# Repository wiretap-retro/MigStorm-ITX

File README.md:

# MigStorm-ITX
A 68000 socketed ITX form factor Minimig.

## Info
Tested by Zenon to boot with Pistorm and CaffeineOS, also with a regular M68k CPU. It appears to be fully working, and I've received feedback from at least 10 people that it is working well in their testing. It could use more general trace cleanup/enhancement, but works as-is.

## Mouser Cart
https://www.mouser.com/ProjectManager/ProjectDetail.aspx?AccessID=da74540bb5 \
At the time of making the Mouser cart, all parts were in stock. If parts go out of stock, EOL, have a part number change, or have a minimum order quantity change -- seach for equivalent replacements or they may be able to be sourced from Arrow and Digikey. I recommend using Octopart and other similar sites to search for parts if you can't find something. I caution using sources like Ebay and Aliexpress for key components, especially from China-based sellers with little to no feedback since they'll often sell counterfeit items. Sometimes you get lucky, sometimes you don't. Primary/authorized retailers are highly recommended for component purchases so you do less troubleshooting and can spend more time playing. \
\
As a DIY project, total cost for all parts and a board should come out to just under $150. (plus the cost of a CPU/Pistorm, power supply, and case) \
\
An interactive HTML BOM has been added to the main repository to assist with building.

## Other / Misc. Contributions
jjsaenz1969's 3D printed case for Migstorm: https://www.thingiverse.com/thing:7063501

## Rev History
v0.6 -- Current rev to build. Updated PS/2 Mouse & Keyboard to use redundant clock & data lines due to issues with some keyboards and mice using splitter style pinout. \
v0.5 -- Updated silkscreen for capacitor polarity upon community request. Updated iBOM and BOM. \
v0.4 -- Corrected PS/2 Mouse & Keyboard pwr/gnd pinout. \
v0.3 -- Changed soft-power circuit from 555 timer to a MAX16054, cleaned up a few traces with lots of vias. Still need more cleanup. [depreciated rev, do not build] \
v0.2 -- Initial rev with corrected 68k socket size. [depreciated rev, do not build] \
v0.1 -- Alpha release, incorrect 68k footprint width. [depreciated, removed]

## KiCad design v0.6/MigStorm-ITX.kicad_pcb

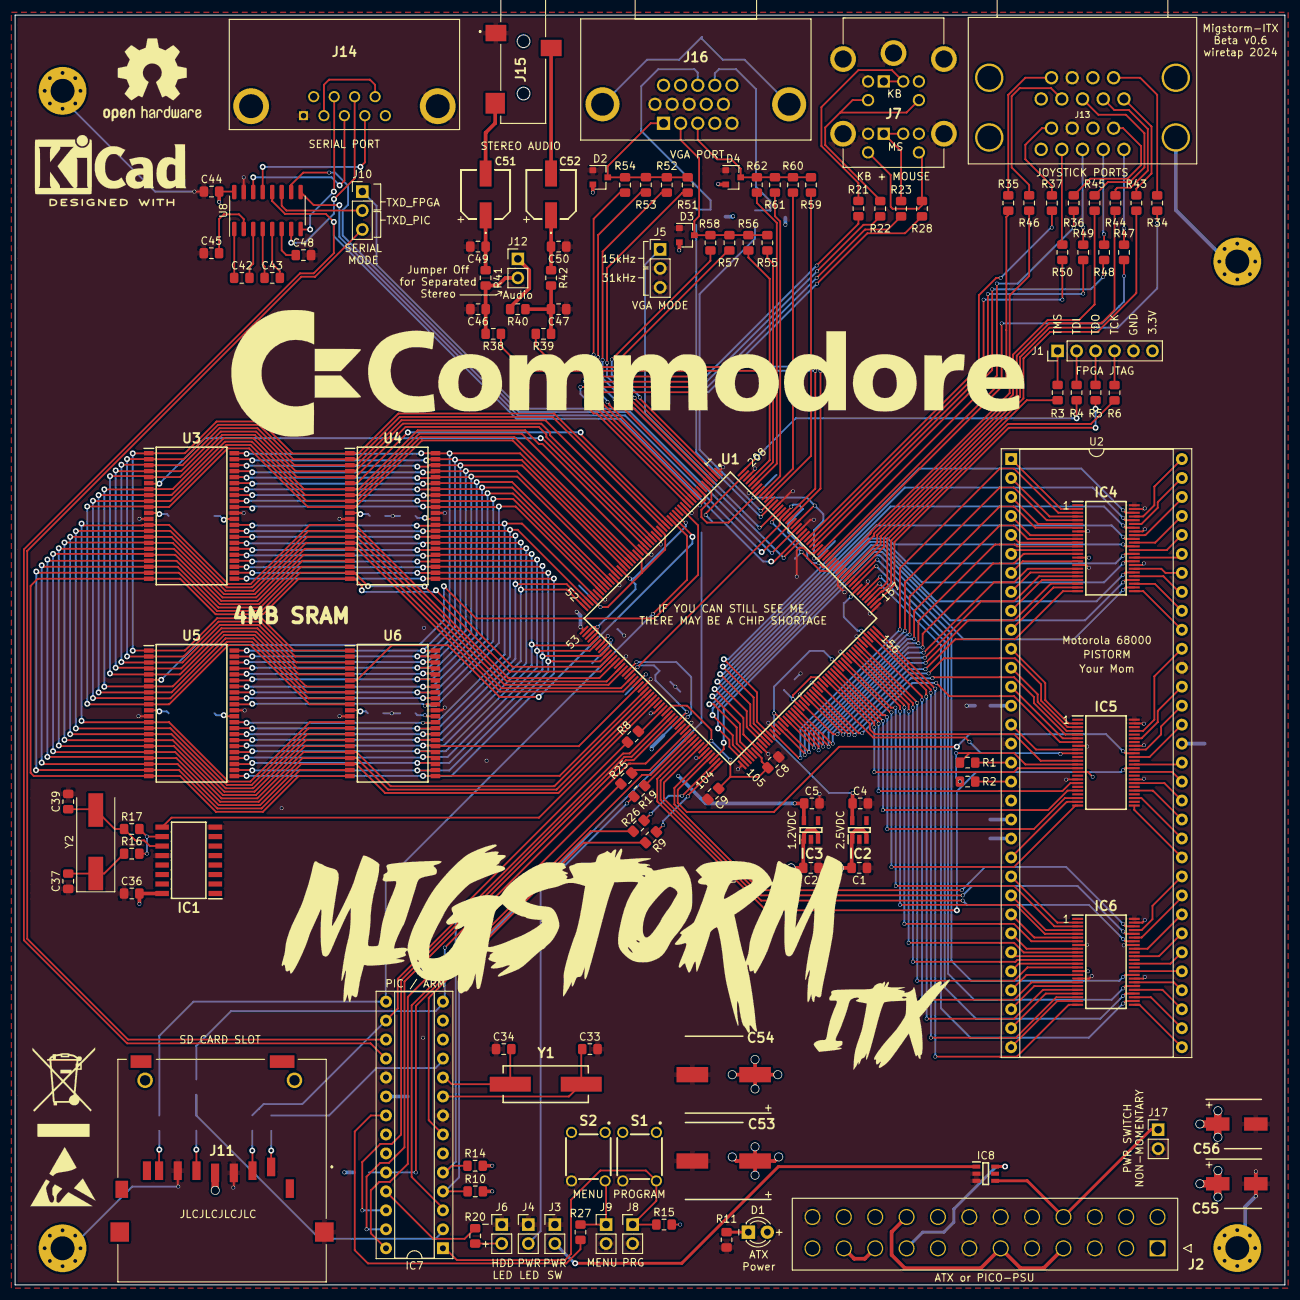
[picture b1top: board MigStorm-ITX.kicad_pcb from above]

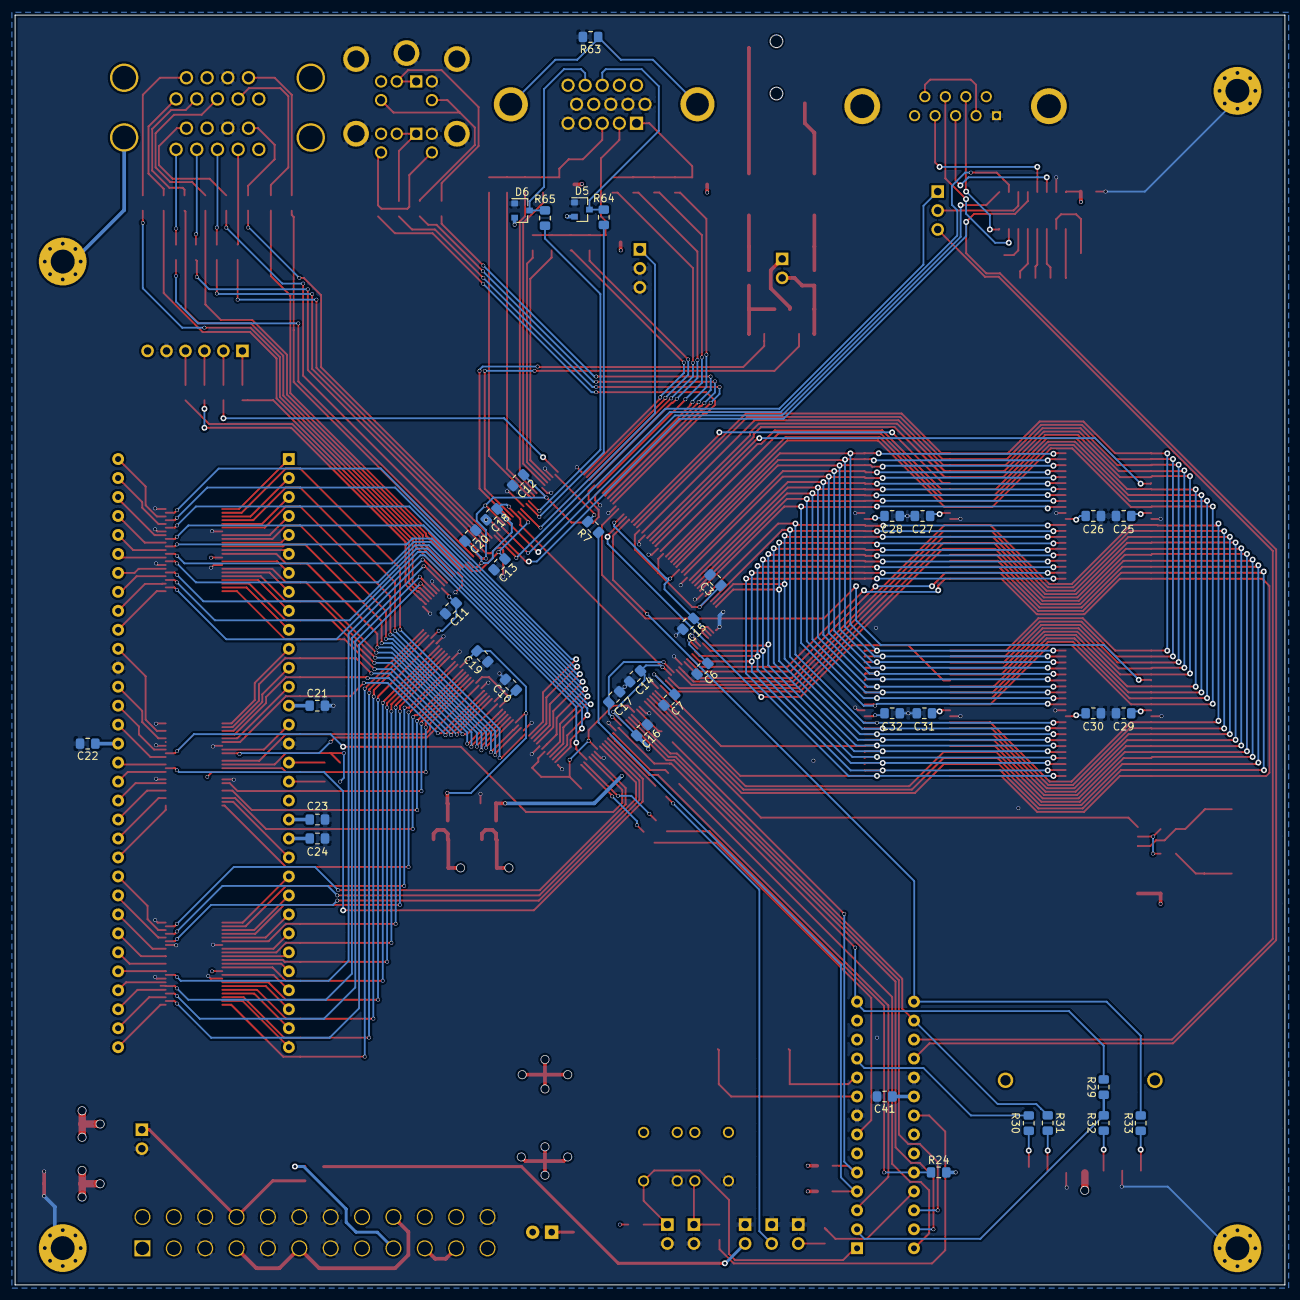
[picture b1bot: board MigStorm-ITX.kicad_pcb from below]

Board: 4 copper layers, 170.0 x 170.0 mm, 157 parts (39 on the bottom side), 282 nets.

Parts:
C1, C2, C4, C5: 1uF X5R; C_0805_2012Metric_Pad1.15x1.40mm_HandSolder
C3, C6, C7, C8, C9, C10, C11, C12, C13, C14, C15, C16, C17, C18, C19, C20, C23, C24, C46, C47, C49, C50: 10nF; C_0805_2012Metric_Pad1.15x1.40mm_HandSolder
C21, C22, C25, C26, C27, C28, C29, C30, C31, C32, C36, C41, C42, C43, C44, C45, C48: 100nF; C_0805_2012Metric_Pad1.15x1.40mm_HandSolder
C33, C34: 47pf; C_0805_2012Metric_Pad1.15x1.40mm_HandSolder
C37: 100pF; C_0805_2012Metric_Pad1.15x1.40mm_HandSolder
C39: 22pF; C_0805_2012Metric_Pad1.15x1.40mm_HandSolder
C51, C52: 16SVT100M; 16SVPT100M
C53, C54: 865230257007; CAPAE1030X1050N
C55, C56: 865230143004; CAPAE660X550N
D1: BrdPwr; LED_D3.0mm
D2, D3, D4, D5, D6: BAV99; SOT-23
IC1: SN74HC4060NSR; SOIC127P780X200-16N
IC2: MIC5504-2.5YM5-TR; SOT95P280X145-5N
IC3: TPS731125DBVR; SOT95P280X145-5N
IC4, IC5, IC6: SN74CBTD16210DGGR; SOP50P810X120-48N
IC7: PIC18F26K20-I_SP; DIP-28_W7.62mm_Socket
IC8: MAX16054AZT+T; SOT95P275X110-6N
J1: JTAG; PinHeader_1x06_P2.54mm_Vertical
J2: 87427-2442
J3: PWRSWCH; PinHeader_1x02_P2.54mm_Vertical
J4: PWRLED; PinHeader_1x02_P2.54mm_Vertical
J5: Video Mode; PinHeader_1x03_P2.54mm_Vertical
J6: DISKLED; PinHeader_1x02_P2.54mm_Vertical
J7: KMDGX-6S_6S-S4N1; KMDGX6S6SS4N1
J8: PROGRAM; PinHeader_1x02_P2.54mm_Vertical
J9: MENU; PinHeader_1x02_P2.54mm_Vertical
J10: Serial; PinHeader_1x03_P2.54mm_Vertical
J11: 500998-0900; 5009980900
J12: Audio; PinHeader_1x02_P2.54mm_Vertical
J13: 178-009-613R571
J14: L77SDE09S1ACO4R
J15: SJ-3523-SMT-TR; SJ3523SMTTR
J16: L77HDE15SD1CH4RHNVGA
J17: ON-OFF; PinHeader_1x02_P2.54mm_Vertical
R1, R2, R16, R52, R56, R60: 2.2k; R_0805_2012Metric_Pad1.15x1.40mm_HandSolder
R3, R4, R5, R6, R33, R65: 100; R_0805_2012Metric_Pad1.15x1.40mm_HandSolder
R7, R8, R9, R21, R22, R23, R25, R26, R27, R28, R30, R31, R32, R34, R35, R36, R37, R43, R44, R45, R46, R47, R48, R49, R50: 270; R_0805_2012Metric_Pad1.15x1.40mm_HandSolder
R10, R14, R15, R24, R51, R55, R59: 4.7k; R_0805_2012Metric_Pad1.15x1.40mm_HandSolder
R11, R29, R40, R53, R57, R61, R63: 1k; R_0805_2012Metric_Pad1.15x1.40mm_HandSolder
R17: 1M; R_0805_2012Metric_Pad1.15x1.40mm_HandSolder
R19, R20: 330; R_0805_2012Metric_Pad1.15x1.40mm_HandSolder
R38, R39, R41, R42, R54, R58, R62: 560; R_0805_2012Metric_Pad1.15x1.40mm_HandSolder
R64: 180; R_0805_2012Metric_Pad1.15x1.40mm_HandSolder
S1, S2: FSM4JH
U1: XC3S400-4PQ208C; QFP50P3060X3060X410-208N
U2: 68000D; DIP-64_W22.86mm_Socket
U3, U4, U5, U6: IS62WV51216EBLL-45TLI; SOP80P1176X120-44N
U8: SP3232EUCN; SOIC-16_3.9x9.9mm_P1.27mm
Y1: LFXTAL035939Reel; LFXTAL020423CUTT
Y2: 4.433619; Crystal_SMD_HC49-SD

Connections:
3.3V: C3.1, C6.1, C7.1, C8.1, C9.1, C10.1, C11.1, C12.1, C25.1, C26.1, C27.1, C28.1, C29.1, C30.1, C31.1, C32.1, C36.1, C41.1, C44.1, C55.1, C56.1, D2.2, D3.2, D4.2, D5.2, D6.2, IC1.16, IC7.20, J1.6, J2.1, J2.2, J2.12, J2.13, J11.4, R10.1, R14.1, R15.1, R24.1, U1.6, U1.23, U1.32, U1.49, U1.60, U1.73, U1.84, U1.98, U1.110, U1.127, U1.136, U1.153, U1.164, U1.177, U1.188, U1.201, U3.11, U3.33, U4.11, U4.33, U5.11, U5.33, U6.11, U6.33, U8.16
5VDC: C1.1, C2.1, C21.1, C22.1, C23.1, C24.1, C53.1, C54.1, D1.2, IC2.1, IC2.3, IC3.1, IC3.3, IC4.15, IC5.15, IC6.15, J2.4, J2.6, J2.21, J2.22, J2.23, J7.A5, J7.B5, J13.7A, J13.7B, U2.14, U2.19, U2.20, U2.21, U2.49
5VSB: IC8.6, J2.9
12VDC: J2.10, J2.11
15KHZ: J5.1, U1.194
+1V2: C5.1, C14.1, C16.1, C18.1, C20.1, IC3.5, U1.70, U1.88, U1.174, U1.192
+2V5: C4.1, C13.1, C15.1, C17.1, C19.1, IC2.5, U1.17, U1.38, U1.54, U1.55, U1.56, U1.69, U1.89, U1.121, U1.142, U1.173, U1.193
A1: IC6.16, U2.29
A2: IC6.19, U2.30
A3: IC6.21, U2.31
A4: IC6.23, U2.32
A5: IC6.25, U2.33
A6: IC6.27, U2.34
A7: IC6.29, U2.35
A8: IC6.31, U2.36
A9: IC6.34, U2.37
A10: IC6.36, U2.38
A11: IC6.38, U2.39
A12: IC6.40, U2.40
A13: IC6.43, U2.41
A14: IC6.45, U2.42
A15: IC5.25, U2.43
A16: IC5.27, U2.44
A17: IC5.29, U2.45
A18: IC5.31, U2.46
A19: IC5.34, U2.47
A20: IC5.36, U2.48
A21: IC5.38, U2.50
A22: IC5.40, U2.51
A23: IC5.43, U2.52
AS: IC4.13, U2.6
AUDIOL: R38.2, U1.191
AUDIOR: R39.2, U1.190
BERR: IC5.23, U2.22
BG: IC5.2, U2.11
BGACK: IC5.4, U2.12
BLUE0: R59.2, U1.198
BLUE1: R60.2, U1.199
BLUE2: R61.2, U1.200
BLUE3: R62.2, U1.203
BR: IC5.6, U2.13
BUTTON: J9.1, R27.1, S2.2
CCLK: R9.2, U1.104
CLK: IC5.9, U2.15
CPU_A1: IC6.33, U1.166
CPU_A2: IC6.30, U1.165
CPU_A3: IC6.28, U1.162
CPU_A4: IC6.26, U1.161
CPU_A5: IC6.24, U1.156
CPU_A6: IC6.22, U1.155
CPU_A7: IC6.20, U1.154
CPU_A8: IC6.18, U1.152
CPU_A9: IC6.14, U1.150
CPU_A10: IC6.12, U1.149
CPU_A11: IC6.10, U1.148
CPU_A12: IC6.7, U1.147
CPU_A13: IC6.5, U1.146
CPU_A14: IC6.3, U1.144
CPU_A15: IC5.24, U1.143
CPU_A16: IC5.22, U1.141
CPU_A17: IC5.20, U1.140
CPU_A18: IC5.18, U1.139
CPU_A19: IC5.14, U1.138
CPU_A20: IC5.12, U1.137
CPU_A21: IC5.10, U1.135
CPU_A22: IC5.7, U1.133
CPU_A23: IC5.5, U1.132
CPU_AS: IC4.35, U1.109
CPU_CLK: IC5.39, U1.101
CPU_D0: IC4.37, U1.111
CPU_D1: IC4.39, U1.113
CPU_D2: IC4.42, U1.114
CPU_D3: IC4.44, U1.115
CPU_D4: IC4.46, U1.116
CPU_D5: IC4.3, U1.117
CPU_D6: IC4.5, U1.119
CPU_D7: IC4.7, U1.120
CPU_D8: IC4.10, U1.122
CPU_D9: IC4.12, U1.123
CPU_D10: IC4.14, U1.124
CPU_D11: IC4.18, U1.125
CPU_D12: IC4.20, U1.126
CPU_D13: IC4.22, U1.128
CPU_D14: IC4.24, U1.130
CPU_D15: IC5.3, U1.131
CPU_DTACK: IC4.26, U1.102
CPU_IPL0: IC6.42, U1.96
CPU_IPL1: IC6.44, U1.97
CPU_IPL2: IC6.46, U1.100
CPU_LDS: IC4.30, U1.107
CPU_RESET: IC5.35, U1.95
CPU_RW: IC4.28, U1.106
CPU_UDS: IC4.33, U1.108
CTS: U1.189, U8.9
D0: IC4.11, U2.5
D1: IC4.9, U2.4
D2: IC4.6, U2.3
D3: IC4.4, U2.2
D4: IC4.2, U2.1
D5: IC4.45, U2.64
D6: IC4.43, U2.63
D7: IC4.40, U2.62
D8: IC4.38, U2.61
D9: IC4.36, U2.60
D10: IC4.34, U2.59
D11: IC4.31, U2.58
D12: IC4.29, U2.57
D13: IC4.27, U2.56
D14: IC4.25, U2.55
D15: IC5.45, U2.54
DIN: R25.1, U1.92
DISKLED: IC7.25, R20.1
DONE: R26.1, U1.103
DTACK: IC4.23, U2.10
FC0: IC6.13, U2.28
FC1: IC6.11, U2.27
FC2: IC6.9, U2.26
FPGA_SEL0: IC7.3, U1.93
FPGA_SEL1: IC7.26, U1.86
FPGA_SEL2: IC7.27, U1.87
GND: C1.2, C2.2, C3.2, C4.2, C5.2, C6.2, C7.2, C8.2, C9.2, C10.2, C11.2, C12.2, C13.2, C14.2, C15.2, C16.2, C17.2, C18.2, C19.2, C20.2, C21.2, C22.2, C23.2, C24.2, C25.2, C26.2, C27.2, C28.2, C29.2, C30.2, C31.2, C32.2, C33.2, C34.1, C36.2, C37.2, C39.2, C41.2, C44.2, C45.1, C46.2, C47.1, C48.1, C49.2, C50.1, C53.2, C54.2, C55.2, C56.2, D2.1, D3.1, D4.1, D5.1, D6.1, IC1.8, IC1.12, IC2.2, IC3.2, IC4.8, IC4.17, IC4.32, IC4.41, IC4.47, IC4.48, IC5.8, IC5.17, IC5.32, IC5.41, IC5.47, IC5.48, IC6.8, IC6.17, IC6.32, IC6.41, IC6.47, IC6.48, IC7.8, IC7.19, IC8.2, IC8.3, J1.5, J2.3, J2.5, J2.7, J2.15, J2.17, J2.18, J2.19, J2.24, J3.1, J4.1, J5.2, J5.3, J6.1, J7.A3, J7.B3, J7.MH1, J7.MH2, J7.MH3, J7.MH4, J7.MH5, J8.2, J9.2, J11.3, J11.6, J11.13, J13.8A, J13.8B, J14.1, J14.MH1, J14.MH2, J15.1, J16.5, J16.6, J16.7, J16.8, J16.10, J17.2, R11.1, R63.2, S1.4, S2.4, U1.1, U1.8, U1.14, U1.25, U1.30, U1.41, U1.47, U1.53, U1.59, U1.66, U1.75, U1.82, U1.91, U1.99, U1.105, U1.112, U1.118, U1.129, U1.134, U1.145, U1.151, U1.157, U1.163, U1.170, U1.179, U1.186, U1.195, U1.202, U1.206, U2.16, U2.53, U3.12, U3.34, U4.12, U4.34, U5.12, U5.34, U6.12, U6.34, U8.15
GREEN0: R55.2, U1.204
GREEN1: R56.2, U1.205
GREEN2: R57.2, U1.2
GREEN3: R58.2, U1.3
HSYNC: R64.1, U1.196
INIT_B: R8.2, U1.83
IPL0: IC6.6, U2.25
IPL1: IC6.4, U2.24
IPL2: IC6.2, U2.23
JOYA0: R46.1, U1.172
JOYA1: R45.1, U1.171
JOYA2: R44.1, U1.169
JOYA3: R43.1, U1.167
JOYA4: R34.2, U1.168
JOYA5: R35.2, U1.175
JOYB0: R50.1, U1.182
JOYB1: R49.1, U1.181
JOYB2: R48.1, U1.180
JOYB3: R47.1, U1.176
JOYB4: R36.2, U1.178
JOYB5: R37.2, U1.183
KBDCLK: R22.2, U1.11
KBDDAT: R21.2, U1.10
LDS: IC4.19, U2.8
MCC_CLKEN: IC7.2, R29.1, R32.2
MCC_SEL: IC7.11, R30.2
MCLK: IC1.9, U1.80
MCLR: IC7.1, J8.1, R15.2, S1.2
MSCLK: R28.1, U1.13
MSDAT: R23.2, U1.12
unnamed: C33.1, IC7.9, Y1.2
unnamed: C34.2, IC7.10, Y1.1
unnamed: C37.1, R16.2, Y2.1
unnamed: C39.1, IC1.11, R17.1, Y2.2
unnamed: C42.1, U8.1
unnamed: C42.2, U8.3
unnamed: C43.1, U8.4
unnamed: C43.2, U8.5
unnamed: C45.2, U8.2
unnamed: C46.1, J12.2, R38.1, R41.2
unnamed: C47.2, R39.1, R40.2, R42.2
unnamed: C48.2, U8.6
unnamed: C49.1, C51.1, R41.1
unnamed: C50.2, C52.1, R42.1
unnamed: C51.2, J15.2
unnamed: C52.2, J15.3
unnamed: D1.1, R11.2
unnamed: D2.3, J16.1, R51.1, R52.1, R53.1, R54.1
unnamed: D3.3, J16.2, R55.1, R56.1, R57.1, R58.1
unnamed: D4.3, J16.3, R59.1, R60.1, R61.1, R62.1
unnamed: D5.3, J16.13, R64.2
unnamed: D6.3, J16.14, R65.2
unnamed: IC1.10, R16.1, R17.2
unnamed: IC7.4, R7.1, R10.2
unnamed: IC7.5, R8.1, R14.2
unnamed: IC7.7, R9.1
unnamed: IC7.21, R27.2
unnamed: IC7.24, R24.2, R26.2
unnamed: IC7.28, R25.2
unnamed: IC8.1, J3.2
unnamed: J1.1, R3.1
unnamed: J1.2, R4.1
unnamed: J1.3, R5.1
unnamed: J1.4, R6.1
unnamed: J4.2, R19.2
unnamed: J6.2, R20.2
unnamed: J7.A1, J7.A2, R21.1
unnamed: J7.A6, J7.A8, R22.1
unnamed: J7.B1, J7.B2, R23.1
unnamed: J7.B6, J7.B8, R28.2
unnamed: J10.2, U8.11
unnamed: J11.1, R30.1
unnamed: J11.2, R31.1
unnamed: J11.5, R32.1
unnamed: J11.7, R33.1
unnamed: J12.1, R40.1
unnamed: J13.1A, R43.2
unnamed: J13.1B, R47.2
unnamed: J13.2A, R44.2
unnamed: J13.2B, R48.2
unnamed: J13.3A, R45.2
unnamed: J13.3B, R49.2
unnamed: J13.4A, R46.2
unnamed: J13.4B, R50.2
unnamed: J13.6A, R34.1
unnamed: J13.6B, R36.1
unnamed: J13.9A, R35.1
unnamed: J13.9B, R37.1
unnamed: J14.3, J14.8
unnamed: J14.4, U8.8
unnamed: J14.5, U8.14
unnamed: J14.6, U8.7
unnamed: J14.7, U8.13
unnamed: J16.MH1, J16.MH2, R63.1
unnamed: R1.1, U2.17
unnamed: R2.1, U2.18
PROG_B: R7.2, U1.207
PS_ON: IC8.4, J2.16, J17.1
PWRLED: R19.1, U1.94
RAM_A1: U1.27, U3.5, U4.5, U5.5, U6.5
RAM_A2: U1.26, U3.4, U4.4, U5.4, U6.4
RAM_A3: U1.24, U3.3, U4.3, U5.3, U6.3
RAM_A4: U1.22, U3.2, U4.2, U5.2, U6.2
RAM_A5: U1.21, U3.1, U4.1, U5.1, U6.1
RAM_A6: U1.35, U3.44, U4.44, U5.44, U6.44
RAM_A7: U1.36, U3.43, U4.43, U5.43, U6.43
RAM_A8: U1.37, U3.42, U4.42, U5.42, U6.42
RAM_A9: U1.57, U3.27, U4.27, U5.27, U6.27
RAM_A10: U1.58, U3.26, U4.26, U5.26, U6.26
RAM_A11: U1.61, U3.25, U4.25, U5.25, U6.25
RAM_A12: U1.62, U3.24, U4.24, U5.24, U6.24
RAM_A13: U1.63, U3.22, U4.22, U5.22, U6.22
RAM_A14: U1.64, U3.21, U4.21, U5.21, U6.21
RAM_A15: U1.79, U3.20, U4.20, U5.20, U6.20
RAM_A16: U1.78, U3.19, U4.19, U5.19, U6.19
RAM_A17: U1.77, U3.18, U4.18, U5.18, U6.18
RAM_A18: U1.76, U3.23, U4.23, U5.23, U6.23
RAM_A19: U1.74, U3.28, U4.28, U5.28, U6.28
RAM_D0: U1.29, U3.7, U4.7, U5.7, U6.7
RAM_D1: U1.31, U3.8, U4.8, U5.8, U6.8
RAM_D2: U1.33, U3.9, U4.9, U5.9, U6.9
RAM_D3: U1.34, U3.10, U4.10, U5.10, U6.10
RAM_D4: U1.65, U3.13, U4.13, U5.13, U6.13
RAM_D5: U1.67, U3.14, U4.14, U5.14, U6.14
RAM_D6: U1.68, U3.15, U4.15, U5.15, U6.15
RAM_D7: U1.71, U3.16, U4.16, U5.16, U6.16
RAM_D8: U1.52, U3.29, U4.29, U5.29, U6.29
RAM_D9: U1.51, U3.30, U4.30, U5.30, U6.30
RAM_D10: U1.50, U3.31, U4.31, U5.31, U6.31
RAM_D11: U1.48, U3.32, U4.32, U5.32, U6.32
RAM_D12: U1.46, U3.35, U4.35, U5.35, U6.35
RAM_D13: U1.45, U3.36, U4.36, U5.36, U6.36
RAM_D14: U1.44, U3.37, U4.37, U5.37, U6.37
RAM_D15: U1.43, U3.38, U4.38, U5.38, U6.38
RAM_LB: U1.42, U3.39, U4.39, U5.39, U6.39
RAM_OE: U1.39, U3.41, U4.41, U5.41, U6.41
RAM_SEL0: U1.28, U3.6
RAM_SEL1: U1.20, U4.6
RAM_SEL2: U1.15, U5.6
RAM_SEL3: U1.18, U6.6
RAM_UB: U1.40, U3.40, U4.40, U5.40, U6.40
RAM_WE: U1.72, U3.17, U4.17, U5.17, U6.17
RED0: R51.2, U1.4
RED1: R52.2, U1.5
RED2: R53.2, U1.7
RED3: R54.2, U1.9
RESET: IC5.13, R1.2, R2.2
RTS: U1.187, U8.10
RW: IC4.21, U2.9
RXD: IC7.18, U1.185, U8.12
SPI_CLK: IC7.14, R29.2, U1.90
SPI_DIN: IC7.16, R31.2, U1.85
SPI_DOUT: IC7.15, R33.2, U1.19
TCK: R6.2, U1.159
TDI: R4.2, U1.208
TDO: R5.2, U1.158
TMS: R3.2, U1.160
TXD: J10.1, U1.184
TXD_MCU: IC7.17, J10.3
UDS: IC4.16, U2.7
VSYNC: R65.1, U1.197

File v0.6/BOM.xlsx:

MigStorm v0.6 Bill of Materials
Reference | Quantity | Value | Footprint | Description | Manufacturer Name | Manufacturer Part Number | Note
C1 C4 C2 C5 | 4 | 1uF X5R | Capacitor_SMD:C_0805_2012Metric_Pad1.15x1.40mm_HandSolder
C14 C16 C18 C20 C13 C15 C17 C19 C3 C6 C7 C8 C9 C10 C11 C12 C23 C24 C46 C47 C49 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 | 22 | 10nF | Capacitor_SMD:C_0805_2012Metric_Pad1.15x1.40mm_HandSolder
C22 C21 C26 C27 C28 C25 C30 C31 C32 C29 C41 C36 C45 C48 C42 C43 C44 | 17 | 100nF | Capacitor_SMD:C_0805_2012Metric_Pad1.15x1.40mm_HandSolder
C33 C34 | 2 | 47pf | Capacitor_SMD:C_0805_2012Metric_Pad1.15x1.40mm_HandSolder
C37 | 1 | 100pF | Capacitor_SMD:C_0805_2012Metric_Pad1.15x1.40mm_HandSolder
C39 | 1 | 22pF | Capacitor_SMD:C_0805_2012Metric_Pad1.15x1.40mm_HandSolder
C51 C52 | 2 | 16SVT100M | 16SVPT100M | Aluminium Organic Polymer Capacitors 16VDC 100uF 20% 780mA 24mOhm | Panasonic | 16SVT100M
C54 C53 | 2 | 470uF | CAPAE1030X1050N | Wurth Elektronik 470uF 10 V dc Aluminium Electrolytic Capacitor, WCAP-AS5H Seri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 | Wurth Elektronik | 865230257007
C55 C56 | 2 | 100uF | CAPAE660X550N | Wurth Elektronik 100uF 6.3 V dc Aluminium Electrolytic Capacitor, WCAP-AS5H Ser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 | Wurth Elektronik | 865230143004
D1 | 1 | BrdPwr | LED_THT:LED_D3.0mm
D6 D5 D2 D3 D4 | 5 | BAV99 | Package_TO_SOT_SMD:SOT-23
IC1 | 1 | SN74HC4060NSR | SOIC127P780X200-16N | 14-Stage Asynchronous Binary Counters And Oscillators | Texas Instruments | SN74HC4060NSR
IC2 | 1 | MIC5504-2.5YM5-TR | SOT95P280X145-5N | LDO Voltage Regulators Single 300mA LDO with Enable Pull-Down & Auto Discharge | Microchip | MIC5504-2.5YM5-TR
IC3 | 1 | TPS731125DBVR | SOT95P280X145-5N | Cap-Free, NMOS, 150mA Low-Dropout (LDO) Regulator With Reverse Current Protecti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 | Texas Instruments | TPS731125DBVR
IC4 IC5 IC6 | 3 | SN74CBTD16210DGGR | SOP50P810X120-48N | SN74CBTD16210DGGR, Bus Switch 74CBT, 10 x 1:1, 4.5 5.5 V 48-Pin TSSOP | Texas Instruments | SN74CBTD16210DGGR
IC7 | 1 | PIC18F26K20-I_SP | Package_DIP:DIP-28_W7.62mm_Socket | Microchip PIC18F26K20-I/SP, 8bit PIC Microcontroller, 64MHz, 64 kB, 1024 B Flas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 | Microchip | PIC18F26K20-I/SP
IC8 | 1 | MAX16054AZT+T | SOT95P275X110-6N | On Off Controller, Debounce, 15kV ESD MAX16054AZT+T, Voltage Supervisor No Push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 | Maxim Integrated | MAX16054AZT+T
J1 | 1 | JTAG | Connector_PinHeader_2.54mm:PinHeader_1x06_P2.54mm_Vertical
J10 | 1 | Serial | Connector_PinHeader_2.54mm:PinHeader_1x03_P2.54mm_Vertical
J11 | 1 | 500998-0900 | 5009980900 | 9 way normal mount SD card connector 9 way normal mount SD card connector | Molex | 500998-0900
J12 | 1 | Audio | Connector_PinHeader_2.54mm:PinHeader_1x02_P2.54mm_Vertical
J13 | 1 | 178-009-613R571 | 178-009-613R571
J14 | 1 | L77SDE09S1ACO4R | L77SDE09S1ACO4R | D-Sub Standard Connectors Dsub, Stamped Signal 3A, Right Angle PCB Thru Hole, F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 | Amphenol | L77SDE09S1ACO4R
J15 | 1 | SJ-3523-SMT-TR | SJ3523SMTTR | Phone Connectors Audio Jacks | CUI Inc. | SJ-3523-SMT-TR
J16 | 1 | L77HDE15SD1CH4RHNVGA | L77HDE15SD1CH4RHNVGA | D-Sub High Density Connectors Dsub, Stamped Signal 3A, High Density, Right Angl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 | Bright Tin Shell | L77HDE15SD1CH4RHNVGA
J17 | 1 | ON-OFF | Connector_PinHeader_2.54mm:PinHeader_1x02_P2.54mm_Vertical
J2 | 1 | 87427-2442 | 87427-2442 | Mini-Fit Jr. Header, 4.20mm Pitch, Vertical, without Flange, 24 Circuits, Tin (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 | Molex | 87427-2442
J3 | 1 | PWRSWCH | Connector_PinHeader_2.54mm:PinHeader_1x02_P2.54mm_Vertical
J4 | 1 | PWRLED | Connector_PinHeader_2.54mm:PinHeader_1x02_P2.54mm_Vertical
J5 | 1 | Video Mode | Connector_PinHeader_2.54mm:PinHeader_1x03_P2.54mm_Vertical
J6 | 1 | DISKLED | Connector_PinHeader_2.54mm:PinHeader_1x02_P2.54mm_Vertical
J7 | 1 | KMDGX-6S_6S-S4N1 | KMDGX6S6SS4N1 | Circular DIN Connectors MINI-DIN PANEL MNT 6P SNAP&LOCK 1270 W | Kycon | KMDGX-6S/6S-S4N1
J8 | 1 | PROGRAM | Connector_PinHeader_2.54mm:PinHeader_1x02_P2.54mm_Vertical
J9 | 1 | MENU | Connector_PinHeader_2.54mm:PinHeader_1x02_P2.54mm_Vertical
R1 R2 R16 R52 R56 R60 | 6 | 2.2k | Resistor_SMD:R_0805_2012Metric_Pad1.15x1.40mm_HandSolder
R11 R40 R29 R63 R53 R57 R61 | 7 | 1k | Resistor_SMD:R_0805_2012Metric_Pad1.15x1.40mm_HandSolder
R15 R14 R10 R24 R51 R55 R59 | 7 | 4.7k | Resistor_SMD:R_0805_2012Metric_Pad1.15x1.40mm_HandSolder
R17 | 1 | 1M | Resistor_SMD:R_0805_2012Metric_Pad1.15x1.40mm_HandSolder
R19 R20 | 2 | 330 | Resistor_SMD:R_0805_2012Metric_Pad1.15x1.40mm_HandSolder
R3 R4 R6 R5 R33 R65 | 6 | 100 | Resistor_SMD:R_0805_2012Metric_Pad1.15x1.40mm_HandSolder
R38 R39 R41 R42 R54 R58 R62 | 7 | 560 | Resistor_SMD:R_0805_2012Metric_Pad1.15x1.40mm_HandSolder
R64 | 1 | 180 | Resistor_SMD:R_0805_2012Metric_Pad1.15x1.40mm_HandSolder
R7 R8 R9 R25 R26 R27 R21 R22 R28 R23 R43 R44 R45 R46 R34 R35 R36 R37 R47 R48 R4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 | 25 | 270 | Resistor_SMD:R_0805_2012Metric_Pad1.15x1.40mm_HandSolder
S1 S2 | 2 | FSM4JH | FSM4JH | 6x6mm tactile switch,5mm H 1.6N Black Button Tactile Switch, SPST-NO 50 mA@ 24 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 | TE Connectivity | FSM4JH
U1 | 1 | XC3S400-4PQ208C | QFP50P3060X3060X410-208N | FPGA - Field Programmable Gate Array 400000 SYSTEM GATE 1.2 VOLT FPGA | XILINX | XC3S400-4PQ208C
U2 | 1 | 68000D | Package_DIP:DIP-64_W22.86mm_Socket
U3 U5 U4 U6 | 4 | IS62WV51216EBLL-45TLI | SOP80P1176X120-44N | SRAM Chip Async Single 2.5V/3.3V 8M-bit 512K x 16 45ns 44-Pin TSOP-II | Integrated Silicon Solution Inc. | IS62WV51216EBLL-45TLI
U8 | 1 | SP3232EUCN | Package_SO:SOIC-16_3.9x9.9mm_P1.27mm
Y1 | 1 | 20 MHz | LFXTAL020423CUTT | Crystals 20MHz 22pF -20C 70C | IQD | LFXTAL035939Reel
Y2 | 1 | 4.433619 MHz | Crystal:Crystal_SMD_HC49-SD |  |  | ABLS-4.433619MHZ-B4-T

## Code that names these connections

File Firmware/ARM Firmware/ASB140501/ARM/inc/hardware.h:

#define MCLK 48000000
#define FWS 1 // Flash wait states

#define DISKLED    AT91C_PIO_PA10
#define MMC_CLKEN  AT91C_PIO_PA24
#define MMC_SEL    AT91C_PIO_PA27
#define DIN AT91C_PIO_PA20
#define CCLK AT91C_PIO_PA4
#define PROG_B AT91C_PIO_PA9
#define INIT_B AT91C_PIO_PA7
#define DONE AT91C_PIO_PA8
#define FPGA0 AT91C_PIO_PA26
#define FPGA1 AT91C_PIO_PA25
#define FPGA2 AT91C_PIO_PA15
#define BUTTON AT91C_PIO_PA28

#define DISKLED_ON *AT91C_PIOA_SODR = DISKLED;
#define DISKLED_OFF *AT91C_PIOA_CODR = DISKLED;
// #define RAMFUNC   __attribute__ ((section(".ramsection")))
#define RAMFUNC __attribute__ ((section (".text.fastcode")))
void init_hardware(void);
void USART_Init(unsigned long baudrate);
void USART_Write(unsigned char c);
void USART_Putc(void* p, char c);
RAMFUNC void SPI_Init(void);
RAMFUNC unsigned char SPI(unsigned char outByte);
RAMFUNC void SPI_Wait4XferEnd(void);
RAMFUNC void EnableCard(void);
RAMFUNC void DisableCard(void);
void EnableFpga(void);
void DisableFpga(void);
void EnableOsd(void);
void DisableOsd(void);
unsigned long CheckButton(void);
void Timer_Init(void);
unsigned long GetTimer(unsigned long offset);
unsigned long CheckTimer(unsigned long t);
void WaitTimer(unsigned long time);

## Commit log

2023-05-09 Interactive BOM for v0.4
2023-10-07 Upload rev 0.5
    Update silk screen for polarity references upon request. Updated iBOM and BOM.
